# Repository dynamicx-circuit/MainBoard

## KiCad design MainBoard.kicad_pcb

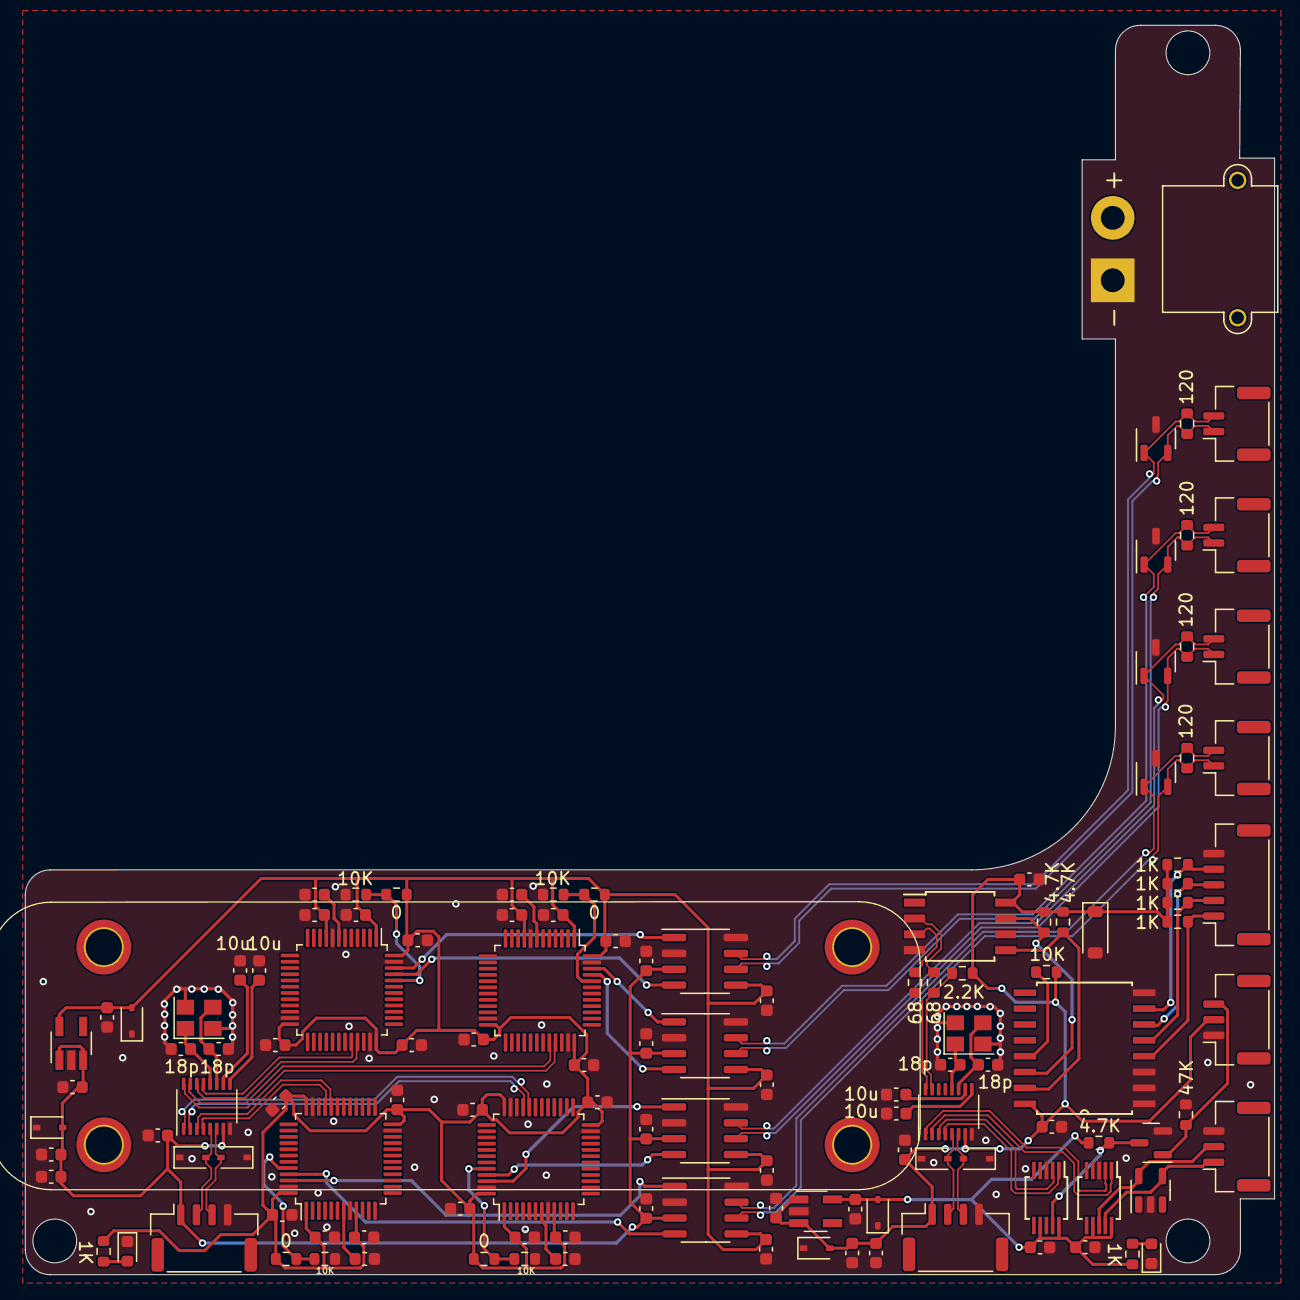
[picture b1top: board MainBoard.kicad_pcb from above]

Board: 2 copper layers, 100.0 x 100.0 mm, 126 parts (0 on the bottom side), 70 nets.

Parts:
C1, C2, C3, C4, C5, C6, C7, C8, C9, C10, C11, C12, C13, C14, C19, C20, C21, C22, C23, C24, C25, C26, C27, C28, C29, C30, C31, C32, C33, C38, C39, C40, C41, C42, C43, C44, C45, C46, C47, C48, C49, C50, C51, C52, C53, C54: 100n; C_0603_1608Metric
C15, C16, C34, C35: 10u; C_0603_1608Metric
C17, C18, C36, C37: 18p; C_0603_1608Metric
D1, D2, D3, D10, D11, D12: BV05C; D_SOD-323
D4, D9: LED; LED_0603_1608Metric
D5, D6: BV03C; D_SOD-323
D7: 5V1; D_SOD-123
J1, J2: Conn_01x04; Molex_CLIK-Mate_502386-0470_1x04-1MP_P1.25mm_Horizontal
J3, J4, J5, J6: Conn_01x02; JST_GH_SM02B-GHS-TB_1x02-1MP_P1.25mm_Horizontal
J7, J8: Conn_01x03; JST_GH_SM03B-GHS-TB_1x03-1MP_P1.25mm_Horizontal
J9: Conn_01x05; JST_GH_SM05B-GHS-TB_1x05-1MP_P1.25mm_Horizontal
J10: Conn_01x02; AMASS_XT30PW-M_1x02_P2.50mm_Horizontal
Q1: S8050; SOT-23
R1, R6, R7, R11, R12, R14: 1K; R_0603_1608Metric
R2, R16, R17: 4.7K; R_0603_1608Metric
R3: 47K; R_0603_1608Metric
R4, R9, R21, R26: 0; R_0603_1608Metric
R5, R10, R15, R22, R27: 10K; R_0603_1608Metric
R8, R13, R25, R30: 120; R_0603_1608Metric
R18: 2.2K; R_0603_1608Metric
R19, R20: 68; R_0603_1608Metric
U1, U11: HX9193; SOT-23-5_HandSoldering
U2, U3: CH340E; MSOP-10_3x3mm_P0.5mm
U4, U7, U13, U15: STM32F072C8Tx; LQFP-48_7x7mm_P0.5mm
U5, U8, U14, U16: TJA1051T-3; SOIC-8_3.9x4.9mm_P1.27mm
U6, U12: SL2.1S; SL2.1S-SSOP-16
U9: ATtiny85V-10S; SOIC-8W_5.3x5.3mm_P1.27mm
U10: PCF8574; SOIC127P1032X265-16N
U17: NUC_Buck; NUC_lm3150
U18, U19, U20, U21: SOT-23-3
U22: SOT-23-5
Y1, Y2: 12M; Crystal_SMD_3225-4Pin_3.2x2.5mm

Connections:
/USB1+: D3.2 (A2), J2.3, U12.6 (UDP)
/USB1-: D2.2 (A2), J2.2, U12.5 (UDM)
/USB2+: D12.2 (A2), J1.3, U6.6 (UDP)
/USB2-: D11.2 (A2), J1.2, U6.5 (UDM)
/USB2CAN/3V3: C8.1, C9.1, C10.1, C11.1, C12.1, C13.1, C21.1, C22.1, C23.1, C24.1, C25.1, C26.1, C33.1, C40.1, C41.1, C42.1, C43.1, C44.1, C45.1, C48.1, C49.1, C50.1, C51.1, C52.1, C53.1, D6.2 (A2), R1.1, R4.2, R9.2, R21.2, R26.2, U4.1 (VBAT), U4.9 (VDDA), U4.24 (VDD), U4.36 (VDDIO2), U4.48 (VDD), U5.5 (VIO), U7.1 (VBAT), U7.9 (VDDA), U7.24 (VDD), U7.36 (VDDIO2), U7.48 (VDD), U8.5 (VIO), U11.5 (VOUT), U13.1 (VBAT), U13.9 (VDDA), U13.24 (VDD), U13.36 (VDDIO2), U13.48 (VDD), U14.5 (VIO), U15.1 (VBAT), U15.9 (VDDA), U15.24 (VDD), U15.36 (VDDIO2), U15.48 (VDD), U16.5 (VIO)
/USB2CAN/STM1_CAN/CAN+: J3.2, R25.1, U14.7 (CANH), U20.1 (H)
/USB2CAN/STM1_CAN/CAN-: J3.1, R25.2, U14.6 (CANL), U20.2 (L)
/USB2CAN/STM1_CAN/CAN_RX: U13.45 (PB8), U14.4 (RXD)
/USB2CAN/STM1_CAN/CAN_TX: U13.46 (PB9), U14.1 (TXD)
/USB2CAN/STM1_CAN/USB_D+: U12.4 (DP1), U13.33 (PA12)
/USB2CAN/STM1_CAN/USB_D-: U12.3 (DM1), U13.32 (PA11)
/USB2CAN/STM2_CAN/CAN+: J4.2, R30.1, U16.7 (CANH), U21.1 (H)
/USB2CAN/STM2_CAN/CAN-: J4.1, R30.2, U16.6 (CANL), U21.2 (L)
/USB2CAN/STM2_CAN/CAN_RX: U15.45 (PB8), U16.4 (RXD)
/USB2CAN/STM2_CAN/CAN_TX: U15.46 (PB9), U16.1 (TXD)
/USB2CAN/STM2_CAN/USB_D+: U12.2 (DP2), U15.33 (PA12)
/USB2CAN/STM2_CAN/USB_D-: U12.1 (DM2), U15.32 (PA11)
/USB2CAN/STM3_CAN/CAN+: J5.2, R13.1, U8.7 (CANH), U19.1 (H)
/USB2CAN/STM3_CAN/CAN-: J5.1, R13.2, U8.6 (CANL), U19.2 (L)
/USB2CAN/STM3_CAN/CAN_RX: U7.45 (PB8), U8.4 (RXD)
/USB2CAN/STM3_CAN/CAN_TX: U7.46 (PB9), U8.1 (TXD)
/USB2CAN/STM3_CAN/USB_D+: U7.33 (PA12), U12.16 (DP3)
/USB2CAN/STM3_CAN/USB_D-: U7.32 (PA11), U12.15 (DM3)
/USB2CAN/STM4_CAN/CAN+: J6.2, R8.1, U5.7 (CANH), U18.1 (H)
/USB2CAN/STM4_CAN/CAN-: J6.1, R8.2, U5.6 (CANL), U18.2 (L)
/USB2CAN/STM4_CAN/CAN_RX: U4.45 (PB8), U5.4 (RXD)
/USB2CAN/STM4_CAN/CAN_TX: U4.46 (PB9), U5.1 (TXD)
/USB2CAN/STM4_CAN/USB_D+: U4.33 (PA12), U12.14 (DP4)
/USB2CAN/STM4_CAN/USB_D-: U4.32 (PA11), U12.13 (DM4)
/USB2CAN/USB_HUB/XIN: C37.1, U12.12 (XIN), Y2.1
/USB2CAN/USB_HUB/XOUT: C36.1, U12.11 (XOUT), Y2.3
/USB2GPIO/3V3: C4.1, C5.1, C6.1, D5.2 (A2), R2.1, R14.1, U1.5 (VOUT), U2.7 (VCC), U2.10 (V3), U3.7 (VCC), U3.10 (V3)
/USB2GPIO/DBUS1/D+: U3.1 (UD+), U6.4 (DP1)
/USB2GPIO/DBUS1/D-: U3.2 (UD-), U6.3 (DM1)
/USB2GPIO/DBUS1/DBus: J7.3, Q1.1 (B), R3.1
/USB2GPIO/GPIO/*D+: R20.1, U9.3 (XTAL2/PB4)
/USB2GPIO/GPIO/*D-: R19.1, U9.2 (XTAL1/PB3)
/USB2GPIO/GPIO/D+: R20.2, U6.16 (DP3)
/USB2GPIO/GPIO/D-: R18.1, R19.2, U6.15 (DM3)
/USB2GPIO/GPIO/P0: J9.1, R6.1, U10.4 (P0)
/USB2GPIO/GPIO/P1: J9.2, R7.2, U10.5 (P1)
/USB2GPIO/GPIO/P2: J9.3, R11.2, U10.6 (P2)
/USB2GPIO/GPIO/P3: J9.4, R12.2, U10.7 (P3)
/USB2GPIO/GPIO/SCL: R17.1, U9.7 (PB2), U10.14 (SCL)
/USB2GPIO/GPIO/SDA: R16.1, U9.5 (AREF/PB0), U10.15 (SDA)
/USB2GPIO/UART1/D+: U2.1 (UD+), U6.2 (DP2)
/USB2GPIO/UART1/D-: U2.2 (UD-), U6.1 (DM2)
/USB2GPIO/UART1/RXD: J8.1, U2.9 (RXD), U22.4 (I/O1)
/USB2GPIO/UART1/TXD: J8.2, U2.8 (TXD), U22.5 (I/O2)
/USB2GPIO/USB_HUB1/XIN: C18.1, U6.12 (XIN), Y1.1
/USB2GPIO/USB_HUB1/XOUT: C17.1, U6.11 (XOUT), Y1.3
/VBUS1: C1.1, C2.1, C14.1, C27.1, C32.1, C38.1, C46.1, C54.1, D1.2 (A2), J2.1, U5.3 (VCC), U8.3 (VCC), U11.1 (VIN), U11.3 (EN), U12.7 (VDD5), U14.3 (VCC), U16.3 (VCC)
/VBUS2: C3.1, C19.1, C28.1, C29.1, C30.1, C31.1, D7.1 (A1), D10.2 (A2), J1.1, J7.2, R6.2, R7.1, R11.1, R12.1, R15.2, R16.2, R17.2, R18.2, U1.1 (VIN), U1.3 (EN), U6.7 (VDD5), U9.8 (VCC), U10.16 (VDD)
GND: C1.2, C2.2, C3.2, C4.2, C5.2, C6.2, C7.1, C8.2, C9.2, C10.2, C11.2, C12.2, C13.2, C14.2, C15.2, C16.2, C17.2, C18.2, C19.2, C20.1, C21.2, C22.2, C23.2, C24.2, C25.2, C26.2, C27.2, C28.2, C29.2, C30.2, C31.2, C32.2, C33.2, C34.2, C35.2, C36.2, C37.2, C38.2, C39.1, C40.2, C41.2, C42.2, C43.2, C44.2, C45.2, C46.2, C47.1, C48.2, C49.2, C50.2, C51.2, C52.2, C53.2, C54.2, D1.1 (A1), D2.1 (A1), D3.1 (A1), D4.1 (K), D5.1 (A1), D6.1 (A1), D7.2 (A2), D9.1 (K), D10.1 (A1), D11.1 (A1), D12.1 (A1), J1.4, J2.4, J7.1, J8.3, J9.5, J10.1, Q1.2 (E), R3.2, R5.1, R10.1, R22.1, R27.1, U1.2 (GND), U2.3 (GND), U3.3 (GND), U4.8 (VSSA), U4.23 (VSS), U4.35 (VSS), U4.47 (VSS), U5.2 (GND), U5.8 (S), U6.8 (VSS), U7.8 (VSSA), U7.23 (VSS), U7.35 (VSS), U7.47 (VSS), U8.2 (GND), U8.8 (S), U9.4 (GND), U10.1 (A0), U10.2 (A1), U10.3 (A2), U10.8 (VSS), U11.2 (GND), U12.8 (VSS), U13.8 (VSSA), U13.23 (VSS), U13.35 (VSS), U13.47 (VSS), U14.2 (GND), U14.8 (S), U15.8 (VSSA), U15.23 (VSS), U15.35 (VSS), U15.47 (VSS), U16.2 (GND), U16.8 (S), U18.3 (GND), U19.3 (GND), U20.3 (GND), U21.3 (GND), U22.2 (GND), Y1.2, Y1.4, Y2.2, Y2.4
unnamed: D4.2 (A), R1.2
unnamed: D9.2 (A), R14.2
unnamed: Q1.3 (C), R2.2, U3.9 (RXD)
unnamed: R4.1, R5.2, U4.44 (BOOT0)
unnamed: C7.2, U4.7 (NRST)
unnamed: C16.1, U6.10 (VDD18)
unnamed: C15.1, U6.9 (VDD33)
unnamed: R9.1, R10.2, U7.44 (BOOT0)
unnamed: C20.2, U7.7 (NRST)
unnamed: R15.1, U10.13 (~INT)
unnamed: C35.1, U12.10 (VDD18)
unnamed: C34.1, U12.9 (VDD33)
unnamed: R21.1, R22.2, U13.44 (BOOT0)
unnamed: C39.2, U13.7 (NRST)
unnamed: R26.1, R27.2, U15.44 (BOOT0)
unnamed: C47.2, U15.7 (NRST)

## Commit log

2023-04-25 Change routings&Add ESD for UART and CAN&Add 5V protection and pull-resistance for GPIO
